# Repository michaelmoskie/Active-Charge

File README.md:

# Active-Charge
Boost Converter, and LiPo charger for use with active guitar pickup systems.

Designed to be charged from 5v source at 500mA.

For use with active pickups, or effects circuits inside of a guitar.

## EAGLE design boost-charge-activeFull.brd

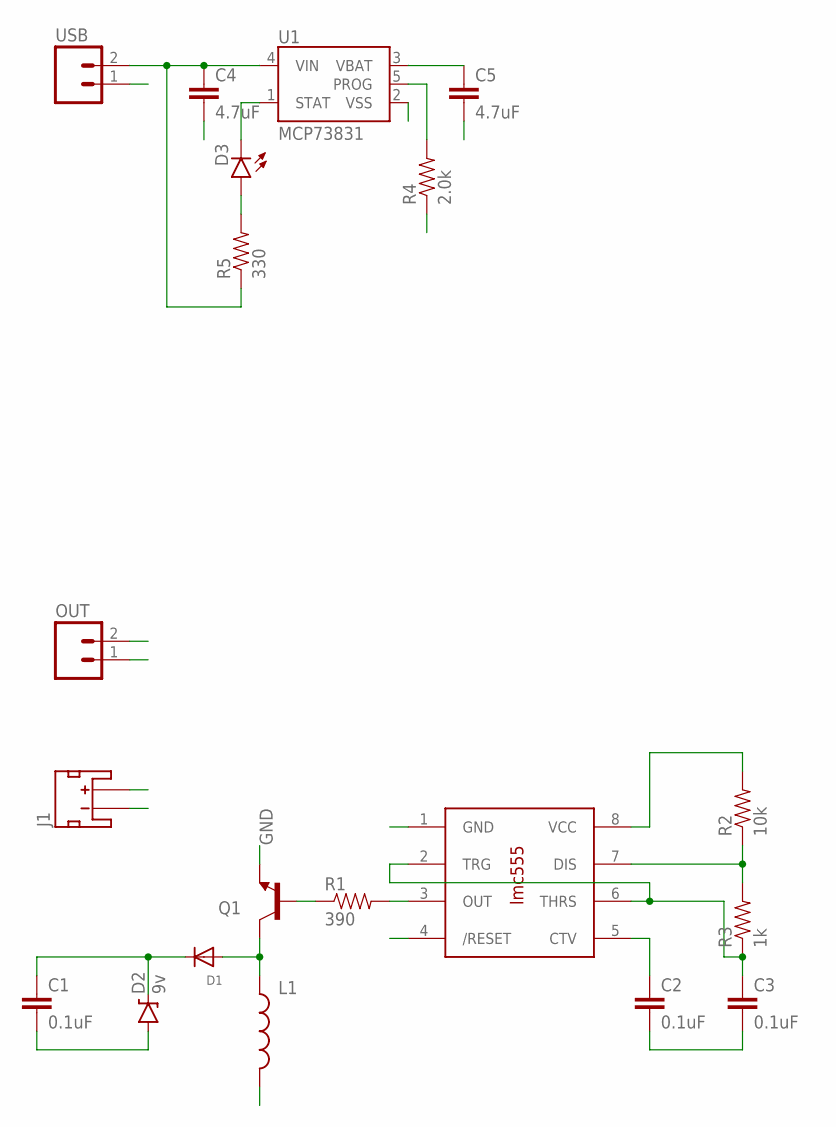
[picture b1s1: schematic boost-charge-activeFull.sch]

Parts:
C1, C2, C3: 0.1uF; 0603-CAP
C4, C5: 4.7uF; 0603-CAP
D1: DIODESOD-323F; SOD-323F
D2: 9v; SOD-323
D3: LED0603; LED-0603
J1: JST_2MM_MALE; JST-2-SMD
L1: INDUCTOR0603; 0603
OUT: M02PTH; 1X02
Q1: TRANSISTOR_NPN2N3904; TO-92
R1: 390; 0603-RES
R2: 10k; 0603
R3: 1k; 0603
R4: 2.0k; 0603-RES
R5: 330; 0603-RES
U1: MCP73831; SOT23-5
U$1: LMC555
USB: M02PTH; 1X02

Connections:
3V: C5.1, J1.2 (+), L1.2, R2.2, U1.3 (VBAT), U$1.4 (/RESET), U$1.8 (VCC)
9V: C1.1, D1.C, D2.C, OUT.2
GND: C1.2, C2.2, C3.2, C4.2, C5.2, D2.A, J1.1 (-), OUT.1, Q1.1 (E), R4.1, U1.2 (VSS), U$1.1 (GND), USB.1
unnamed: R4.2, U1.5 (PROG)
unnamed: D1.A, L1.1, Q1.3 (C)
unnamed: R1.2, U$1.3 (OUT)
unnamed: Q1.2 (B), R1.1
unnamed: C3.1, R3.1, U$1.2 (TRG), U$1.6 (THRS)
unnamed: C2.1, U$1.5 (CTV)
unnamed: R2.1, R3.2, U$1.7 (DIS)
unnamed: D3.C, U1.1 (STAT)
unnamed: D3.A, R5.2
VCC: C4.1, R5.1, U1.4 (VIN), USB.2

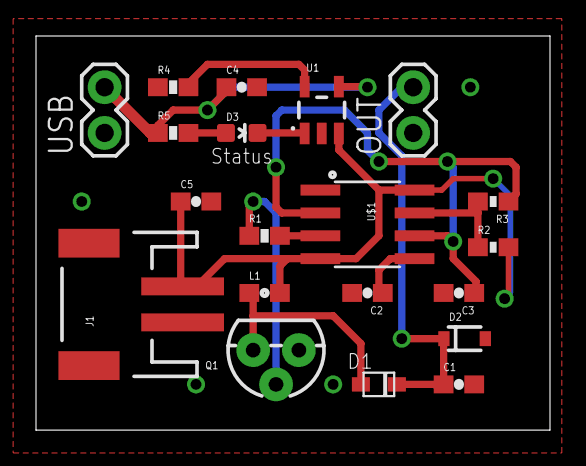
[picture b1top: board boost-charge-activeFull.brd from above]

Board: 2 copper layers, 28.6 x 21.9 mm, 20 parts (0 on the bottom side), 13 nets.

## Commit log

2015-10-17 Initial commit of prototype
2015-10-17 Added library with custom parts for this project
2015-10-17 Added board image
2015-10-17 Connected trigger
2015-10-18 New Board Image

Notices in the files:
parts and their libraries:
SparkFun-Capacitors: Licensing: Creative Commons ShareAlike 4.0 International - https://creativecommons.org/licenses/by-sa/4.0
